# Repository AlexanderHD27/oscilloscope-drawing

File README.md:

# Oscilloscope Drawing

A device that draws on an oscilloscope.

## Introduction
Drawing on analog oscilloscope is almost a classic in the electronics/microcontroller community now.
This is done by setting the scope to XY-Mode and then controlling the X/Y-deflection of the electron-beam. My Scope has no Z-Channel. I cannot control the intensity of beam (or switches off) by voltage yet

This Project is my shot at this. I use custom hardware (build on perf-board) to archive this goal. I have build
a 2-Channel 16bit DAC with an refresh rate of around 1 MSample per second. Further more a usb-interface + driver shall be developed.

My current todo list can be found [here](TODO.md)

### Hardware

Everything is solder onto pref-boards an connected via pin-headers and jumpers

(Diagram of the System-Hardware components)

The DACs are R-2R-Ladder DAC on a made custom PCB. The Input-Bits are feed from Octal-D-Latches ([74HC573](https://www.reichelt.de/oktal-d-type-latch-3-state-2--6-v-dil-20-74hc-573-p3264.html?search=74HC573)) in combination with some other logic ICs to reduce pin usage on the RPi Pico. Data sent via a 8-bit a parallel Bus to

<br>

At 1 MHz Square Wave, the analog output signal quality is significantly degraded. Testing revealed that probably R-2R_Ladder DAC is the weak link and needs further improvement. I currently use R = 11kOhm.

Yellow: X-Channel, Blue: Y-Channel, Magenta: Digital Input Signal to the DAC. (Yellow and Blue are coupled to AC, they usually to remove the 2.5V offset)

For testing the optics I did use a Hameg MH 312 Oscilloscope (I got this one used from Kleinanzeigen, so its already falling apart: semi-broken Coupling-switch, not being able focus the beam correctly, X-Pos nob falling off all the time)

### Further Components
- [Firmware](./firmware/README.md):

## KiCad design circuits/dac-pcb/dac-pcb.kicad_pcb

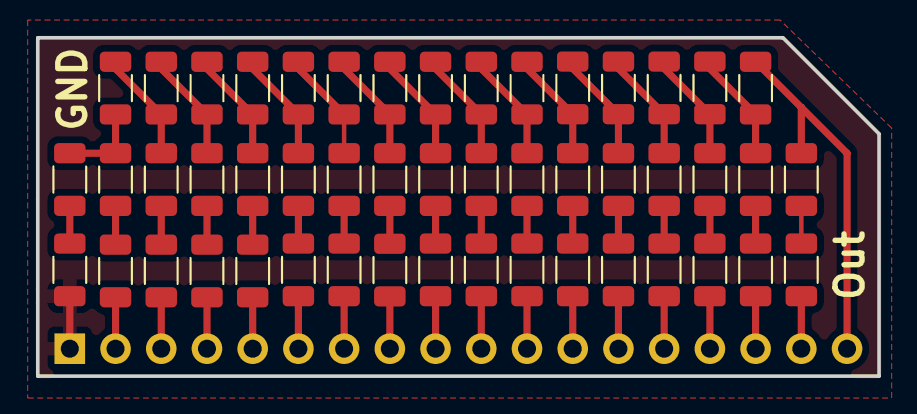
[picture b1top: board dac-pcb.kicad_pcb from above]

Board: 2 copper layers, 46.7 x 18.8 mm, 50 parts (1 on the bottom side), 50 nets.

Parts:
J1: Conn_01x18; PinHeader_1x18_P2.54mm_Horizontal
R1, R2, R3, R4, R5, R6, R7, R8, R9, R10, R11, R12, R13, R14, R15, R16, R17, R18, R19, R20, R21, R22, R23, R24, R25, R26, R27, R28, R29, R30, R31, R32, R33, R34, R35, R36, R37, R38, R39, R40, R41, R42, R43, R44, R45, R46, R47, R48, R49: 10k; R_1206_3216Metric

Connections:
GND: J1.1, R2.2
unnamed: J1.2, R4.2
unnamed: J1.3, R7.2
unnamed: J1.4, R10.2
unnamed: J1.5, R13.2
unnamed: J1.6, R16.2
unnamed: J1.7, R19.2
unnamed: J1.8, R22.2
unnamed: J1.9, R25.2
unnamed: J1.10, R28.2
unnamed: J1.11, R31.2
unnamed: J1.12, R34.2
unnamed: J1.13, R37.2
unnamed: J1.14, R40.2
unnamed: J1.15, R43.2
unnamed: J1.16, R46.2
unnamed: J1.17, R49.2
unnamed: J1.18, R47.2, R48.1
unnamed: R1.1, R3.1, R5.1
unnamed: R1.2, R2.1
unnamed: R3.2, R4.1
unnamed: R5.2, R6.1, R8.1
unnamed: R6.2, R7.1
unnamed: R9.2, R10.1
unnamed: R8.2, R9.1, R11.1
unnamed: R11.2, R12.1, R14.1
unnamed: R12.2, R13.1
unnamed: R14.2, R15.1, R17.1
unnamed: R15.2, R16.1
unnamed: R17.2, R18.1, R20.1
unnamed: R18.2, R19.1
unnamed: R20.2, R21.1, R23.1
unnamed: R21.2, R22.1
unnamed: R23.2, R24.1, R26.1
unnamed: R24.2, R25.1
unnamed: R26.2, R27.1, R29.1
unnamed: R27.2, R28.1
unnamed: R29.2, R30.1, R32.1
unnamed: R30.2, R31.1
unnamed: R32.2, R33.1, R35.1
unnamed: R33.2, R34.1
unnamed: R35.2, R36.1, R38.1
unnamed: R36.2, R37.1
unnamed: R38.2, R39.1, R41.1
unnamed: R39.2, R40.1
unnamed: R41.2, R42.1, R44.1
unnamed: R42.2, R43.1
unnamed: R44.2, R45.1, R47.1
unnamed: R45.2, R46.1
unnamed: R48.2, R49.1
